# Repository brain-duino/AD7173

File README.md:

# brain-duino-kicad-test
A preliminary playground to test EAGLE xml to KiCAD conversion for the brain-duino circuits

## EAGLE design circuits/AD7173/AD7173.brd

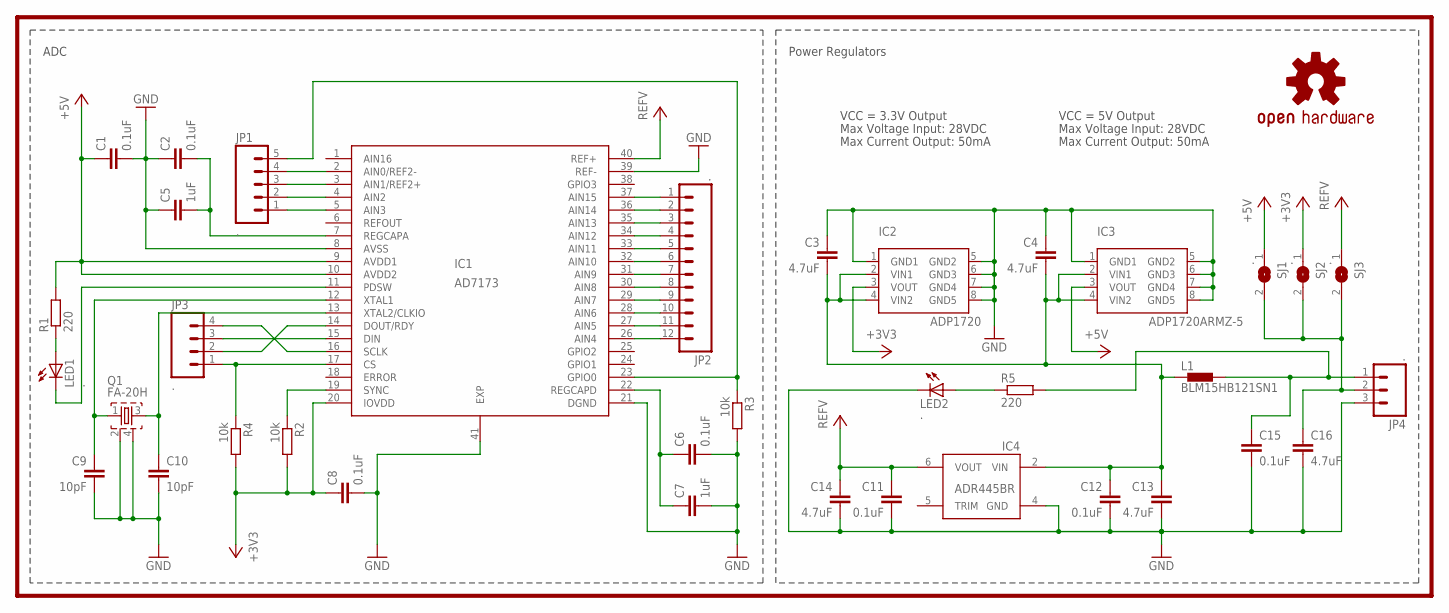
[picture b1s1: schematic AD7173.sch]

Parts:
C1, C2, C6, C8, C11, C12, C15: 0.1uF; C0402
C3, C4, C13, C14, C16: 4.7uF; C0402
C5, C7: 1uF; C0402
C9, C10: 10pF; C0402
IC1: AD7173; LFCSP_WQ6X6MM
IC2: ADP1720; MSOP08
IC3: ADP1720ARMZ-5; MSOP08
IC4: ADR445BR; SO8
JP1: .; 1X05
JP2: .; 1X12
JP3: .; 1X04
JP4: .; 1X03
L1: BLM15HB121SN1; 0402
LED1, LED2: .; CHIP-LED0603
LOGO1: OSHW-LOGOS; OSHW-LOGO-S
Q1: FA-20H
R1, R5: 220; R0402
R2, R3, R4: 10k; R0402
SJ1, SJ2, SJ3: .; SJ

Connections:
+3V3: C8.1, IC1.20 (IOVDD), IC2.3 (VOUT), R2.2, R4.2, SJ2.1
+5V: C1.1, IC1.9 (AVDD1), IC1.10 (AVDD2), IC3.3 (VOUT), R1.2, SJ1.1
GND: C1.2, C2.1, C3.1, C4.1, C5.1, C6.2, C7.2, C8.2, C9.2, C10.2, C11.2, C12.2, C13.2, C14.2, C15.2, C16.2, IC1.8 (AVSS), IC1.21 (DGND), IC1.39 (REF-), IC1.41 (EXP), IC2.1 (GND1), IC2.5 (GND2), IC2.6 (GND3), IC2.7 (GND4), IC2.8 (GND5), IC3.1 (GND1), IC3.5 (GND2), IC3.6 (GND3), IC3.7 (GND4), IC3.8 (GND5), IC4.4 (GND), JP4.3, LED2.C, Q1.2, Q1.4, R3.2
unnamed: LED1.A, R1.1
unnamed: IC1.17 (CS), JP3.1, R4.1
unnamed: IC1.37 (AIN15), JP2.1
unnamed: IC1.23 (GPIO0), JP1.5, R3.1
unnamed: C2.2, C5.2, IC1.7 (REGCAPA)
unnamed: IC1.36 (AIN14), JP2.2
unnamed: IC1.35 (AIN13), JP2.3
unnamed: IC1.34 (AIN12), JP2.4
unnamed: IC1.33 (AIN11), JP2.5
unnamed: IC1.32 (AIN10), JP2.6
unnamed: IC1.31 (AIN9), JP2.7
unnamed: IC1.30 (AIN8), JP2.8
unnamed: IC1.29 (AIN7), JP2.9
unnamed: IC1.28 (AIN6), JP2.10
unnamed: IC1.27 (AIN5), JP2.11
unnamed: IC1.26 (AIN4), JP2.12
unnamed: IC1.5 (AIN3), JP1.1
unnamed: IC1.4 (AIN2), JP1.2
unnamed: IC1.3 (AIN1/REF2+), JP1.3
unnamed: IC1.2 (AIN0/REF2-), JP1.4
unnamed: C10.1, IC1.13 (XTAL2/CLKIO), Q1.3
unnamed: IC1.14 (DOUT/RDY), JP3.2
unnamed: IC1.15 (DIN), JP3.3
unnamed: IC1.16 (SCLK), JP3.4
unnamed: C9.1, IC1.12 (XTAL1), Q1.1
unnamed: C16.1, JP4.2, SJ1.2, SJ2.2, SJ3.2
unnamed: C15.1, JP4.1, L1.2, R5.2
unnamed: LED2.A, R5.1
unnamed: C6.1, C7.1, IC1.22 (REGCAPD)
unnamed: IC1.19 (SYNC), R2.1
SPI: IC1.11 (PDSW), LED1.C
VCC: C11.1, C14.1, IC1.40 (REF+), IC4.6 (VOUT), SJ3.1
VIN: C3.2, C4.2, C12.1, C13.1, IC2.2 (VIN1), IC2.4 (VIN2), IC3.2 (VIN1), IC3.4 (VIN2), IC4.2 (VIN), L1.1

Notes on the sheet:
Power Regulators
ADC
VCC = 3.3V Output
Max Current Output: 50mA
Max Voltage Input: 28VDC
VCC = 5V Output

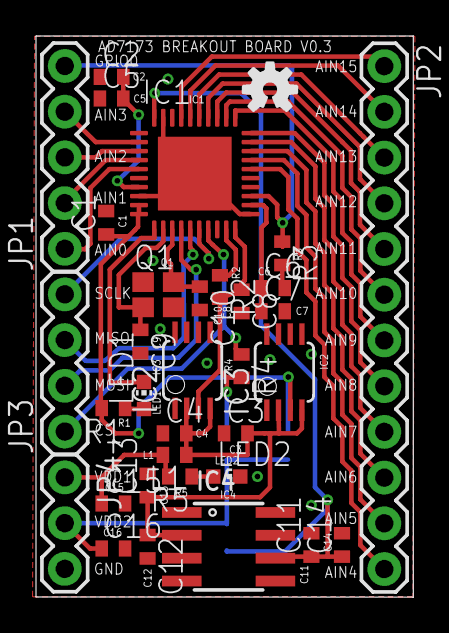
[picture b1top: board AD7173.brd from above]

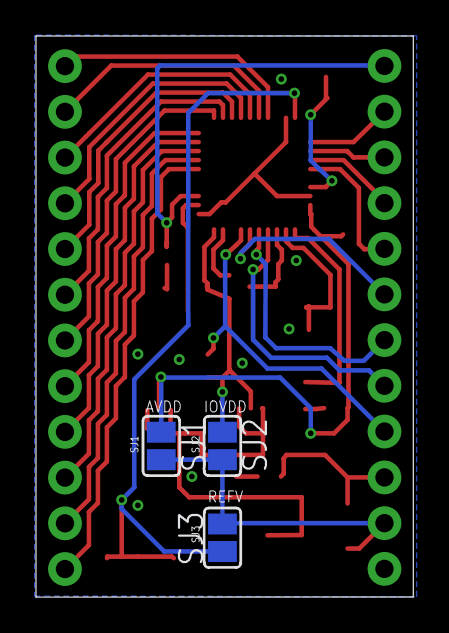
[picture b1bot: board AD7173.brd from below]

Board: 2 copper layers, 21.0 x 31.2 mm, 37 parts (3 on the bottom side), 36 nets.

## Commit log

2015-03-25 Create gh-pages branch via GitHub
2015-12-26 Fixed some ERC errors, approved others. Caught some missing dots and duplicate wire segments. Added dummy value "." to devices where ERC requires value. Color might be more informative value for LEDs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
2015-12-26 Added dummy values for components where ERC requires them.
2015-12-26 parameters AutoGrid, Efforts and TopRouterVariant got erased This is probably an artifact of me not using the auto router. Separate commit, so it can be undone.
2015-12-26 capture eagle.epf for AD7173 circuit (may be platform specific, integrate with caution)
2015-12-28 Convert AD7173.brd using https://github.com/DanChianucci/Eagle2Kicad
2015-12-28 PoC: produce Gerber and drill files from AD7173KiCad.brd No settings changed from my pcbnew defaults
2015-12-28 AD7173KiCad.brd after running pcbnew, and saving after exporting Gerber and drill files
2015-12-28 PoC: produce postscript files from AD7173KiCad.brd Settings changed from my pcbnew defaults.
2015-12-28 AD7173KiCad.brd after running pcbnew, and saving after exporting postscript layer files
2016-01-02 a library generated from schematic-file-converter from eaglexml to kicad
2016-01-02 empty KiCAD project to start with
2016-01-02 create empty KiCAD schematic by starting eeschema
2016-01-02 copy gatestka-cache.lib to gatestka.lib
2016-01-02 add gatestka.lib to kicad-test project library path
2016-01-02 AD7173KiCAD-cache.lib and AD7173KiCAD.sch , result of python2 -m upconvert.upconverter -i ~/ExG/EEG/brain-duino/AD7173/circuits/AD7173/AD7173.sch -f eaglexml -o AD7173KiCad.sch -t kicad --unsupported
    Should be identical to gatestka-cache.lib created before with different output file name

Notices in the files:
parts and their libraries:
SparkFun-Aesthetics: Licensing: Creative Commons ShareAlike 4.0 International - https://creativecommons.org/licenses/by-sa/4.0
